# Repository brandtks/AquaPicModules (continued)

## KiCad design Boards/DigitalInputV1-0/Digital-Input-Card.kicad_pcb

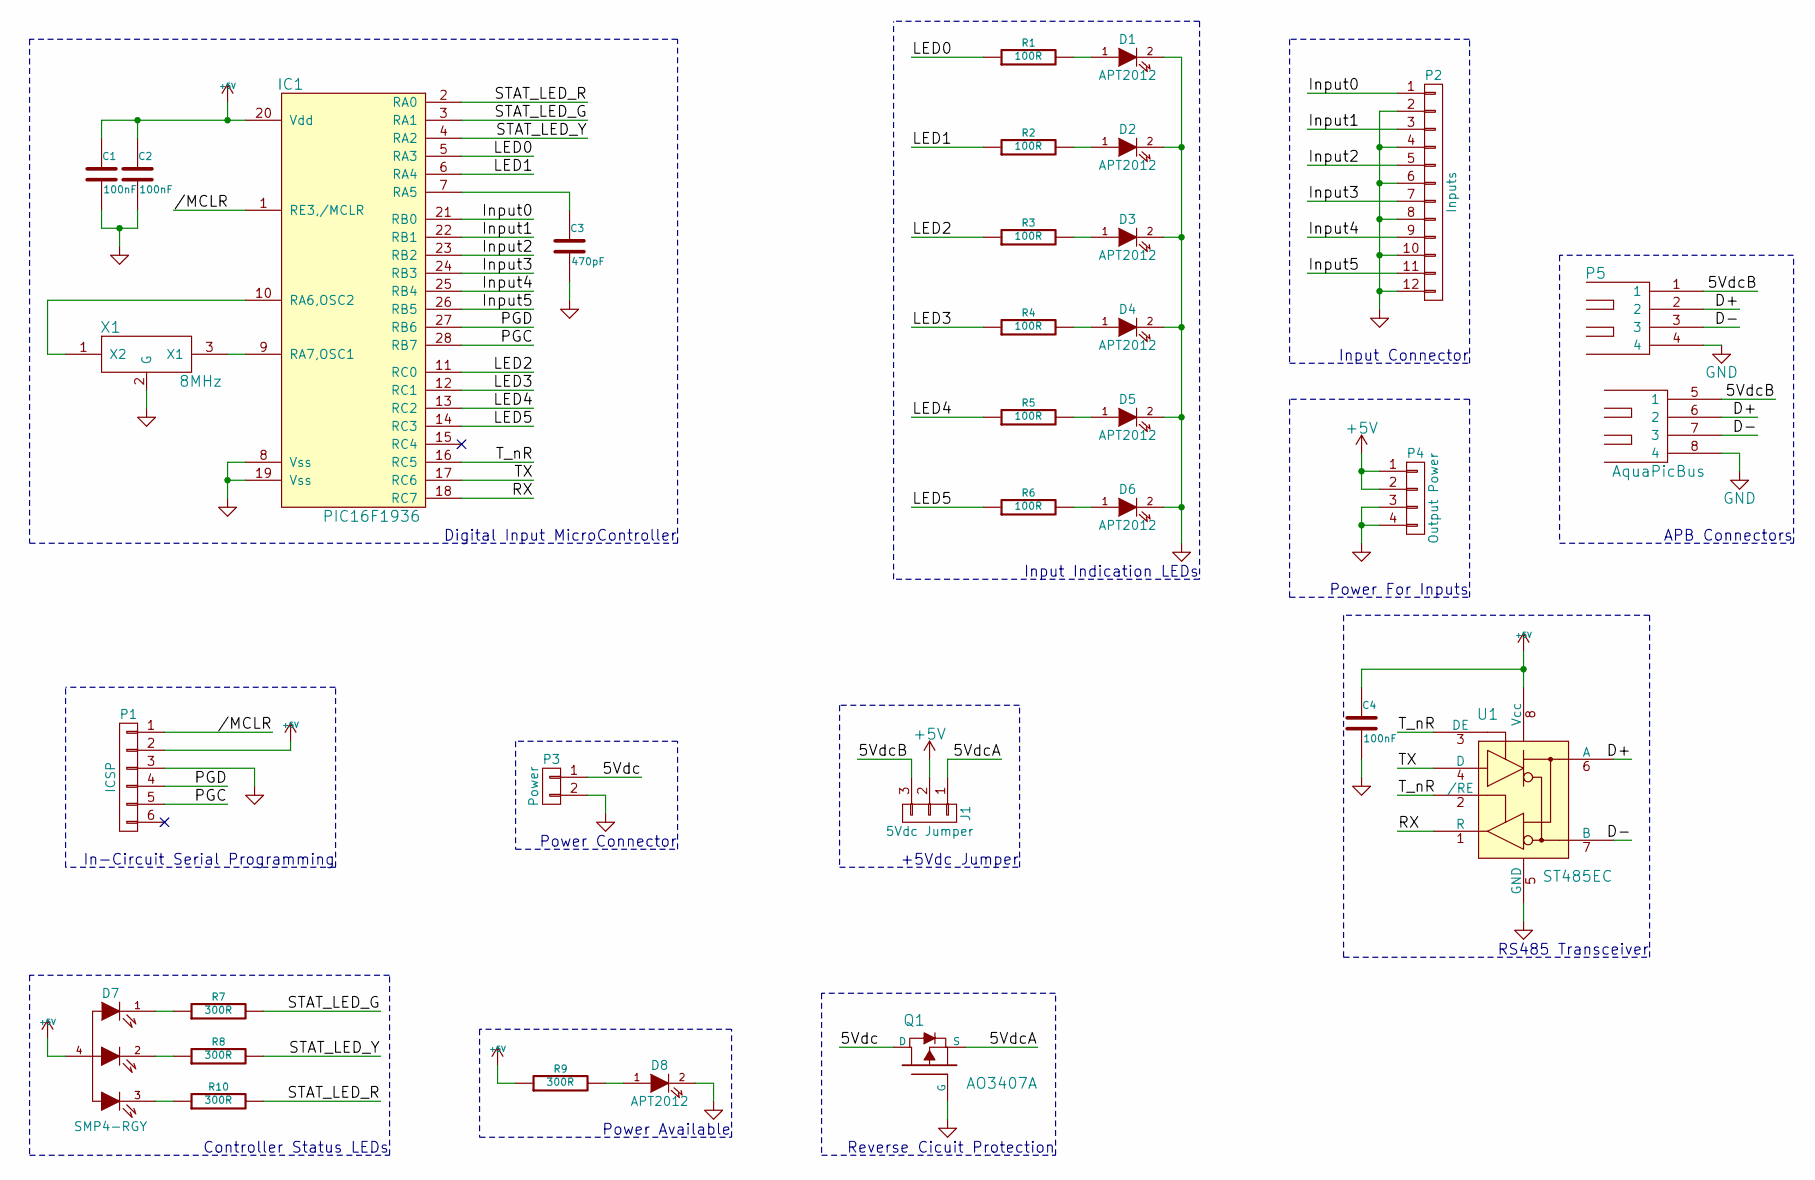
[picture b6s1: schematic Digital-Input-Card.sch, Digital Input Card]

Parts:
C1, C2, C4: 100nF; C_0805
C3: 470pF; C_0805
D1, D2, D3, D4, D5, D6, D8: APT2012; LED-0805
D7: SMP4-RGY; PLCC-4
IC1: PIC16F1936; SOIC-28_7.5x17.9mm_Pitch1.27mm
J1: 5Vdc Jumper; Pin_Header_Straight_1x03
P1: ICSP; Pin_Header_Straight_1x06
P2: Inputs; Screw_Header_1x12
P3: Power; Screw_Header_1x2
P4: Output Power; Screw_Header_1x4
P5: AquaPicBus; USB-1.1_Stacked
Q1: AO3407A; SOT-23
R1, R2, R3, R4, R5, R6: 100R; R_0805
R7, R8, R9, R10: 300R; R_0805
U1: ST485EC; SOIC-8_3.9x4.9mm_Pitch1.27mm
X1: 8MHz; Resonator_3.2x1.3

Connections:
+5V: C1.1, C2.1, C4.1, D7.4, IC1.20 (Vdd), J1.2, P1.2, P4.1, P4.2, R9.1, U1.8 (Vcc)
/5Vdc: P3.1, Q1.3 (D)
/5VdcA: J1.1, Q1.2 (S)
/5VdcB: J1.3, P5.1, P5.5 (1)
//MCLR: IC1.1 (RE3,/MCLR), P1.1
/D+: P5.2, P5.6 (2), U1.6 (A)
/D-: P5.3, P5.7 (3), U1.7 (B)
/Input0: IC1.21 (RB0), P2.1
/Input1: IC1.22 (RB1), P2.3
/Input2: IC1.23 (RB2), P2.5
/Input3: IC1.24 (RB3), P2.7
/Input4: IC1.25 (RB4), P2.9
/Input5: IC1.26 (RB5), P2.11
/LED0: IC1.5 (RA3), R1.1
/LED1: IC1.6 (RA4), R2.1
/LED2: IC1.11 (RC0), R3.1
/LED3: IC1.12 (RC1), R4.1
/LED4: IC1.13 (RC2), R5.1
/LED5: IC1.14 (RC3), R6.1
/PGC: IC1.28 (RB7), P1.5
/PGD: IC1.27 (RB6), P1.4
/RX: IC1.18 (RC7), U1.1 (R)
/STAT_LED_G: IC1.3 (RA1), R7.2
/STAT_LED_R: IC1.2 (RA0), R10.2
/STAT_LED_Y: IC1.4 (RA2), R8.2
/TX: IC1.17 (RC6), U1.4 (D)
/T_nR: IC1.16 (RC5), U1.2 (/RE), U1.3 (DE)
GND: C1.2, C2.2, C3.2, C4.2, D1.2 (K), D2.2 (K), D3.2 (K), D4.2 (K), D5.2 (K), D6.2 (K), D8.2 (K), IC1.8 (Vss), IC1.19 (Vss), P1.3, P2.2, P2.4, P2.6, P2.8, P2.10, P2.12, P3.2, P4.3, P4.4, P5.4, P5.8 (4), Q1.1 (G), U1.5 (GND), X1.2 (G)
unnamed: C3.1, IC1.7 (RA5)
unnamed: D1.1 (A), R1.2
unnamed: D2.1 (A), R2.2
unnamed: D3.1 (A), R3.2
unnamed: D4.1 (A), R4.2
unnamed: D5.1 (A), R5.2
unnamed: D6.1 (A), R6.2
unnamed: D7.1, R7.1
unnamed: D7.2, R8.1
unnamed: D7.3, R10.1
unnamed: D8.1 (A), R9.2
unnamed: IC1.9 (RA7,OSC1), X1.3 (X1)
unnamed: IC1.10 (RA6,OSC2), X1.1 (X2)

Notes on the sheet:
In-Circuit Serial Programming
Input Indication LEDs
Digital Input MicroController
Input Connector
Controller Status LEDs
RS485 Transceiver
Reverse Cicuit Protection
Power Available
+5Vdc Jumper
Power Connector
APB Connectors
Power For Inputs

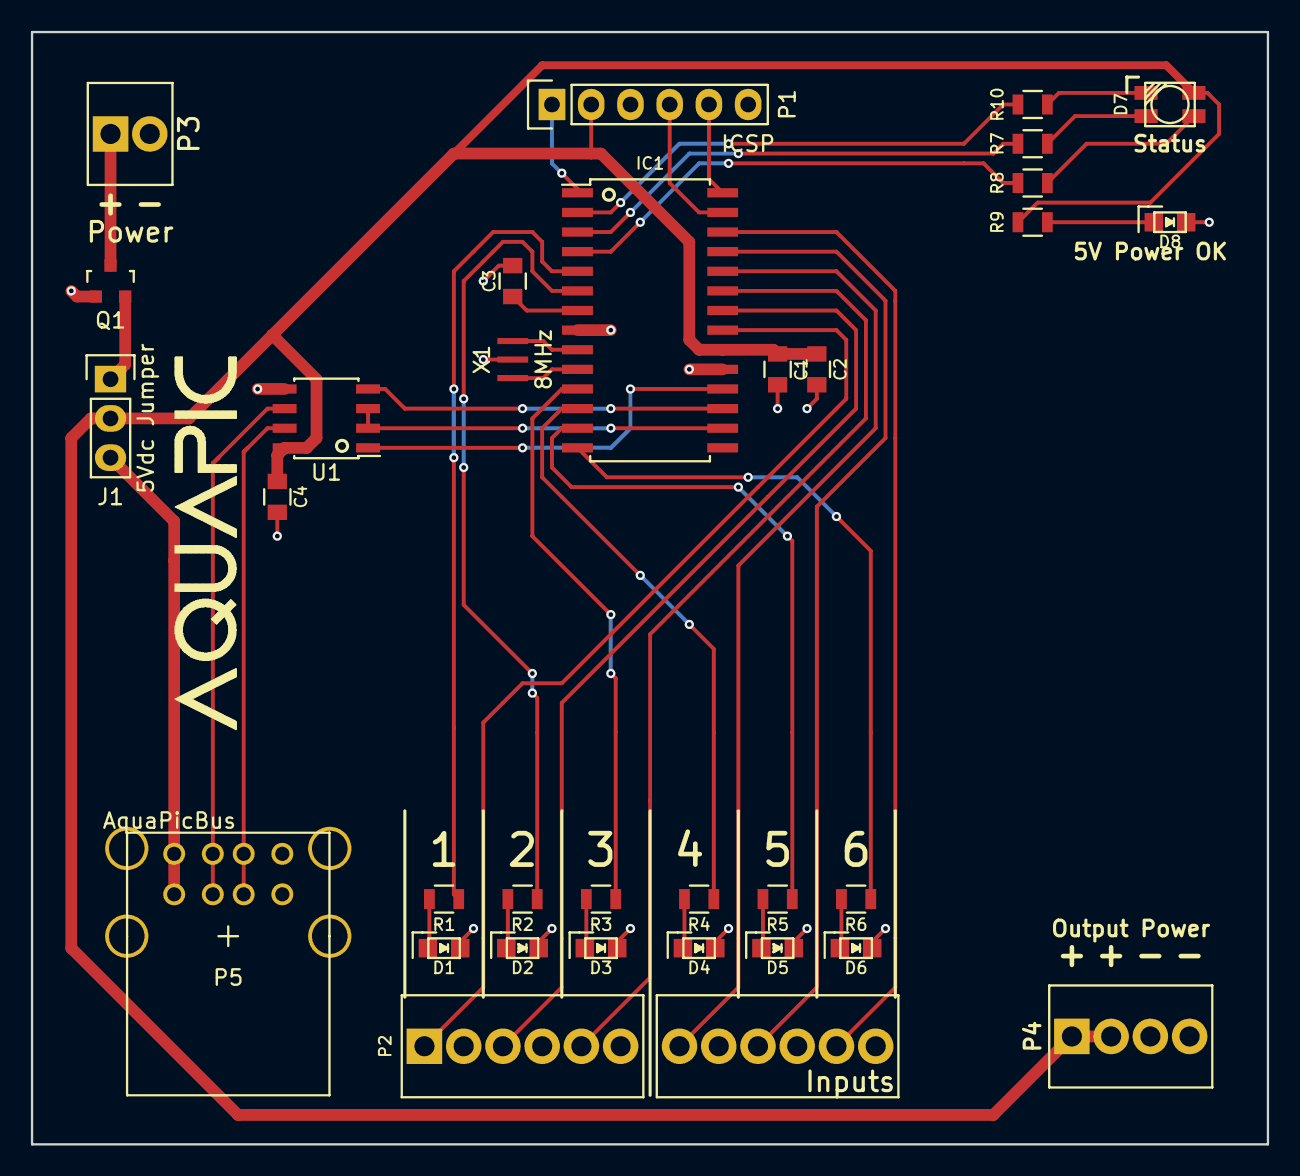
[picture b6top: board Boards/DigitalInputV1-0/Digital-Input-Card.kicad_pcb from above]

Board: 2 copper layers, 80.0 x 72.0 mm, 33 parts (0 on the bottom side), 41 nets.

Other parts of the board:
LOGO: Val**; AquaPic_Logo

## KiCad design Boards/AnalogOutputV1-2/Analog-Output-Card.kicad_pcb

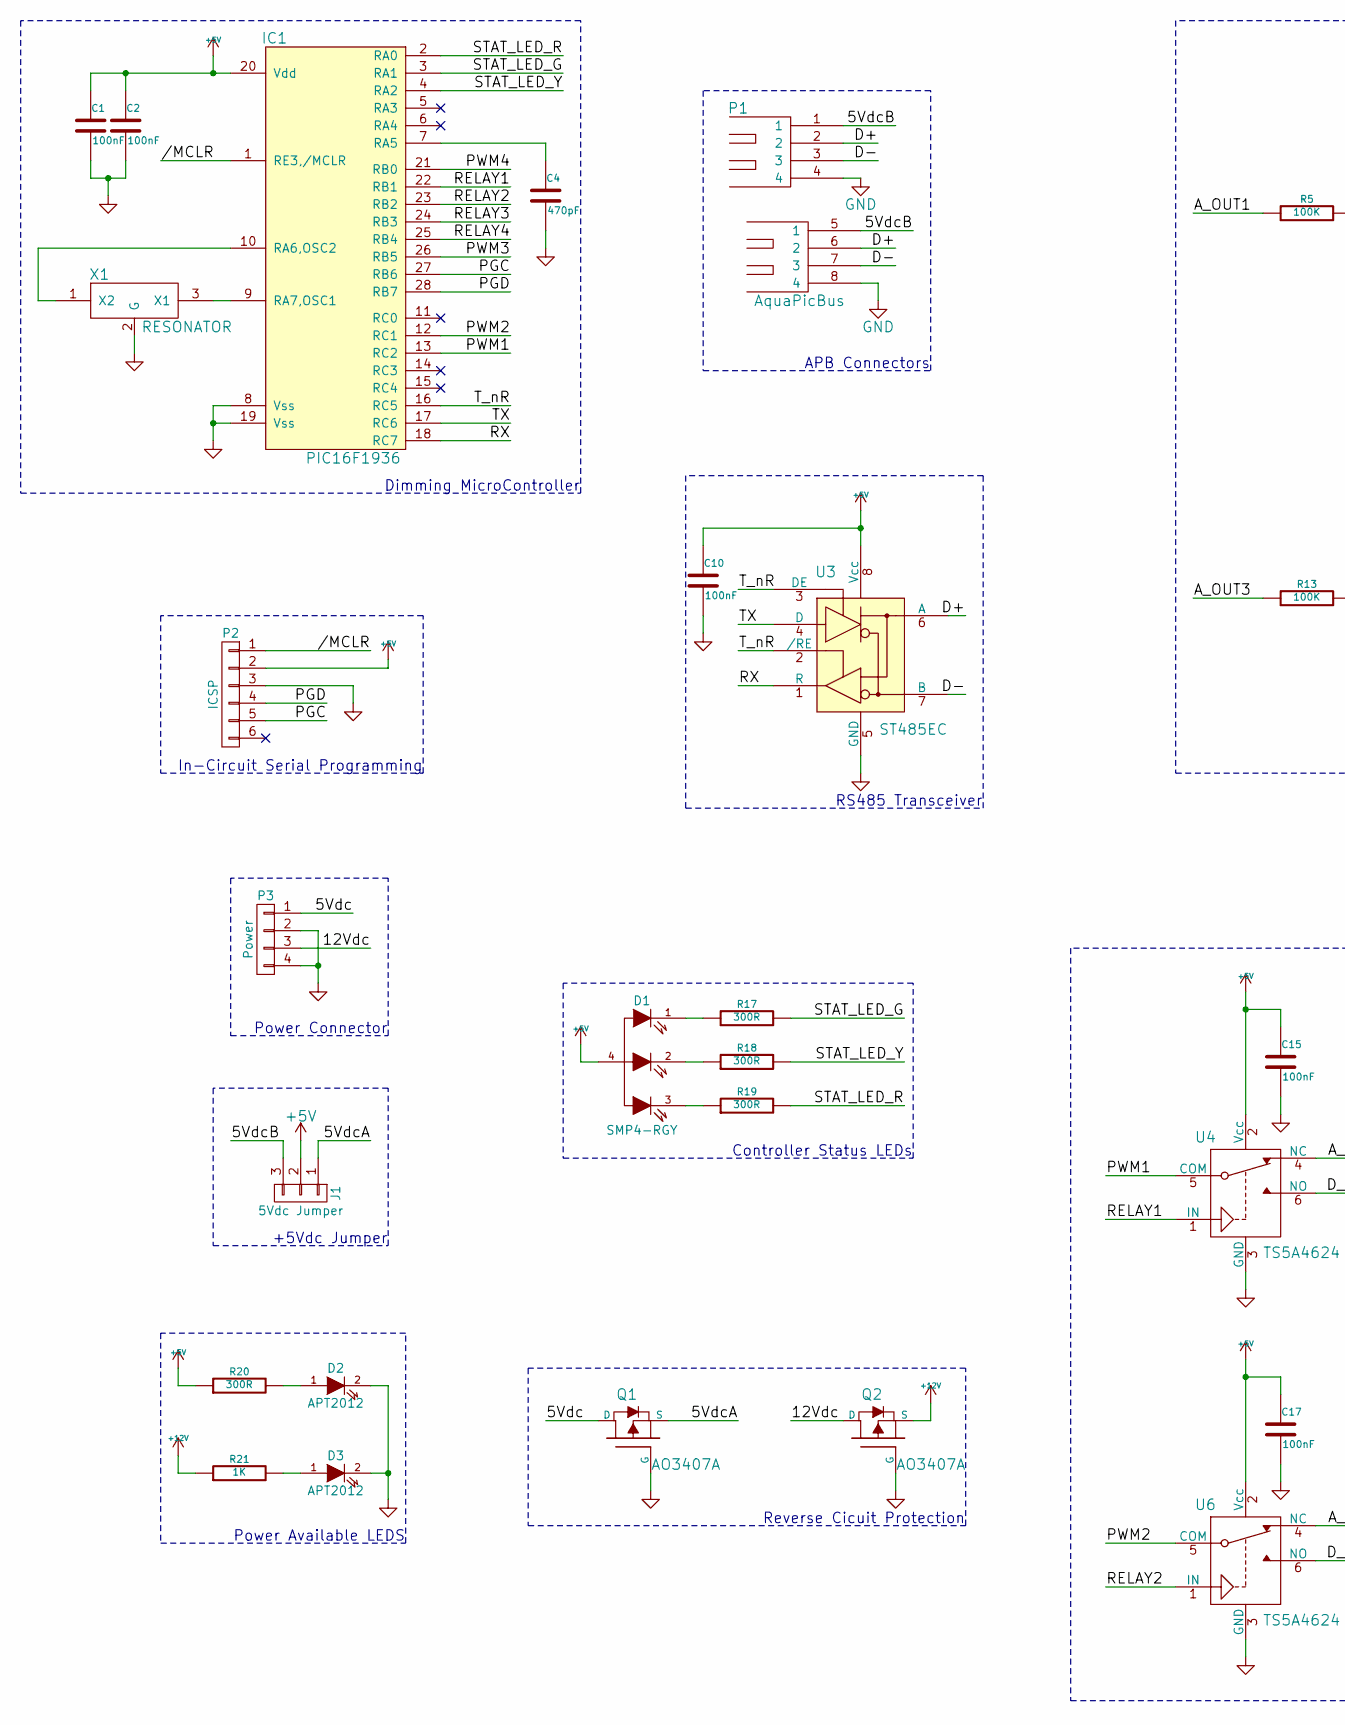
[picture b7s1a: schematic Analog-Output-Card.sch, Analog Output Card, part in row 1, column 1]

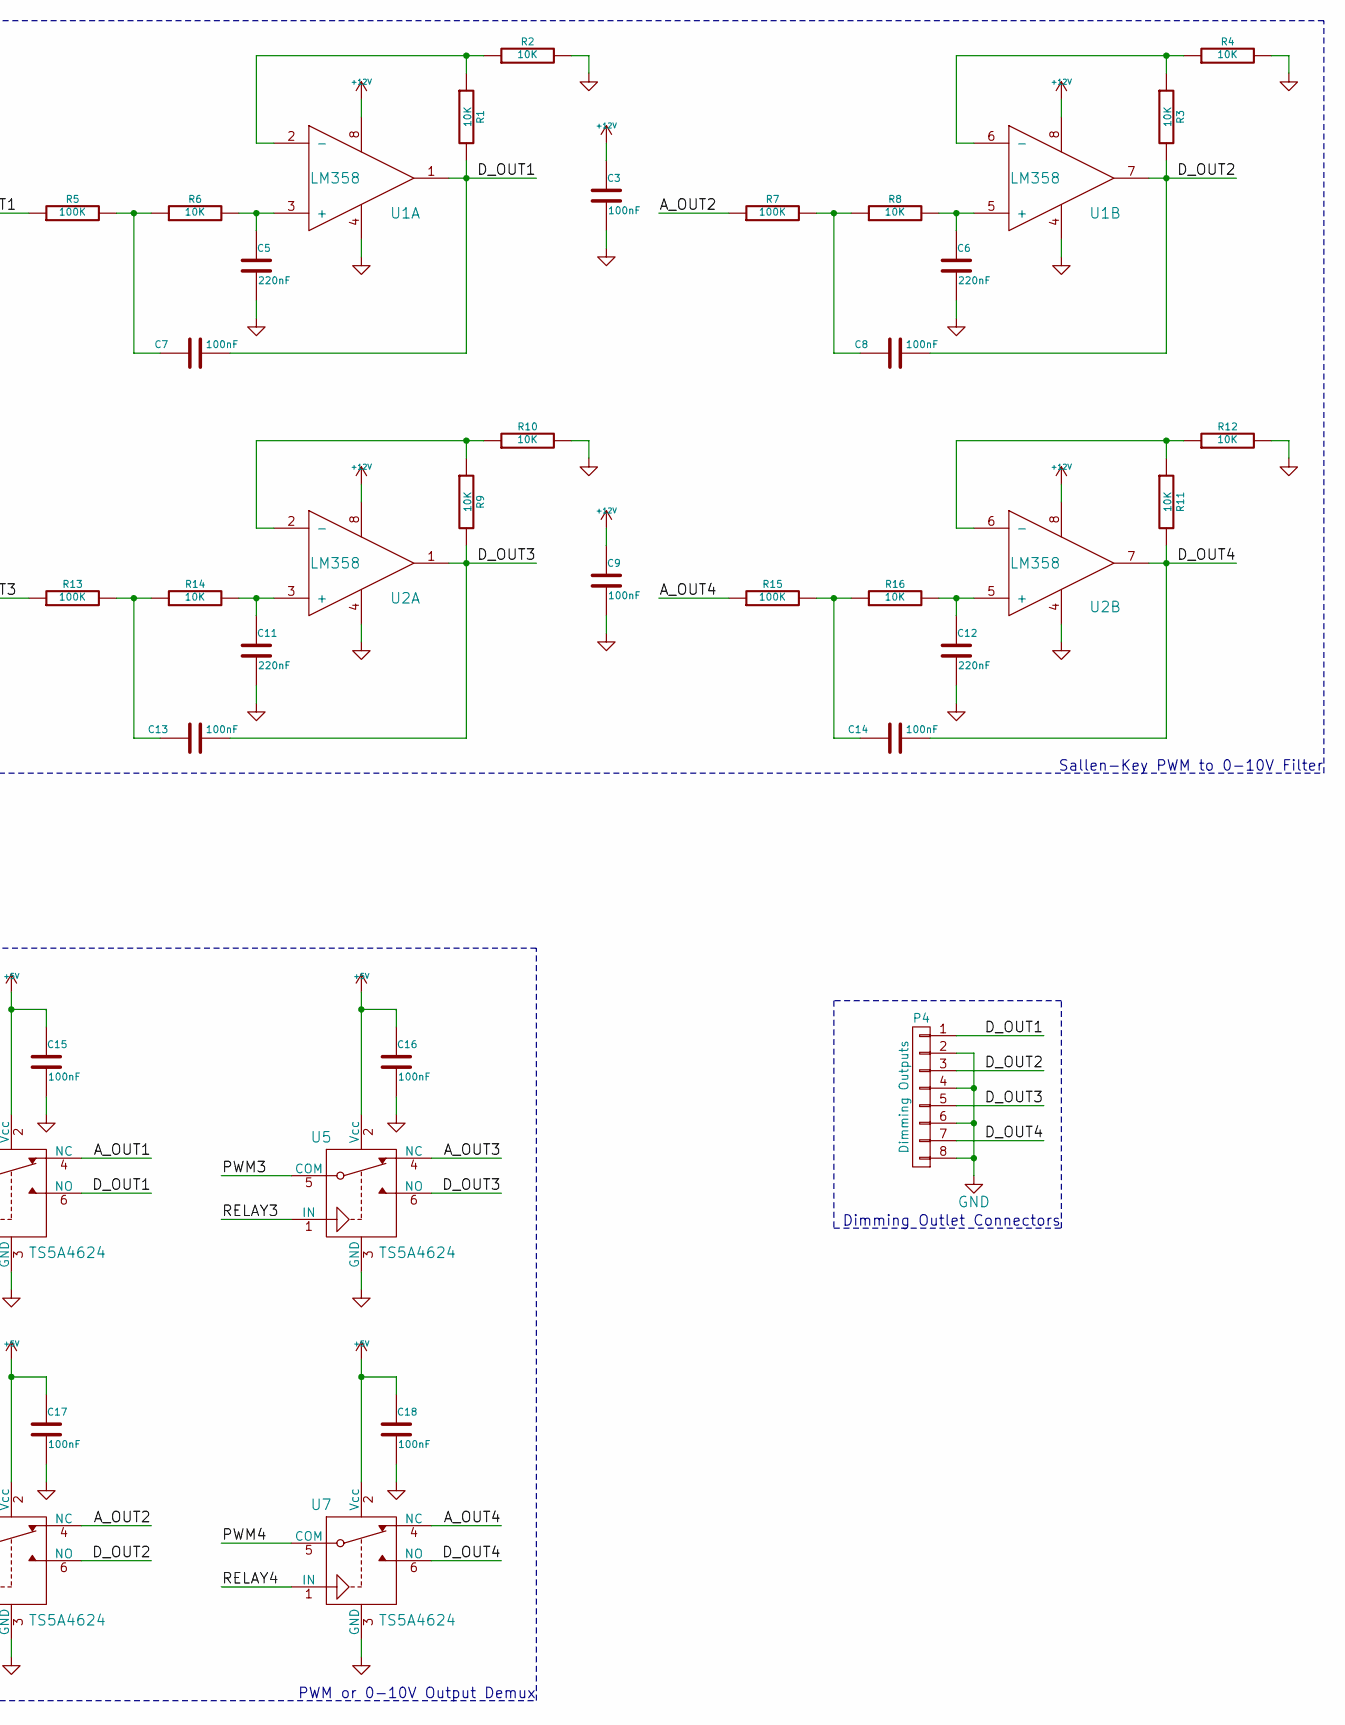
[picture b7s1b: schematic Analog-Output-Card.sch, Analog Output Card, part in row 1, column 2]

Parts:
C1, C2, C3, C7, C8, C9, C10, C13, C14, C15, C16, C17, C18: 100nF; C_0805
C4: 470pF; C_0805
C5, C6, C11, C12: 220nF; C_0805
D1: SMP4-RGY; PLCC-4
D2, D3: APT2012; LED-0805
IC1: PIC16F1936; SOIC-28_7.5x17.9mm_Pitch1.27mm
J1: 5Vdc Jumper; Pin_Header_Straight_1x03
P1: AquaPicBus; USB-1.1_Stacked
P2: ICSP
P3: Power; Screw_Header_1x4
P4: Dimming Outputs; Screw_Header_1x8
Q1, Q2: AO3407A; SOT-23
R1, R2, R3, R4, R6, R8, R9, R10, R11, R12, R14, R16: 10K; R_0805
R5, R7, R13, R15: 100K; R_0805
R17, R18, R19, R20: 300R; R_0805
R21: 1K; R_0805
U1, U2: LM358; TSSOP-8_4.4x3mm_Pitch0.65mm
U3: ST485EC; SOIC-8_3.9x4.9mm_Pitch1.27mm
U4, U5, U6, U7: TS5A4624; TSSOP-6_SC-70-6
X1: RESONATOR

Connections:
+5V: C1.1, C2.1, C10.1, C15.1, C16.1, C17.1, C18.1, D1.4, IC1.20 (Vdd), J1.2, P2.2, R20.1, U3.8 (Vcc), U4.2 (Vcc), U5.2 (Vcc), U6.2 (Vcc), U7.2 (Vcc)
+12V: C3.1, C9.1, Q2.2 (S), R21.1, U1.8, U2.8
/5Vdc: P3.1, Q1.3 (D)
/5VdcA: J1.1, Q1.2 (S)
/5VdcB: J1.3, P1.1, P1.5 (1)
/12Vdc: P3.3, Q2.3 (D)
//MCLR: IC1.1 (RE3,/MCLR), P2.1
/A_OUT1: R5.1, U4.4 (NC)
/A_OUT2: R7.1, U6.4 (NC)
/A_OUT3: R13.1, U5.4 (NC)
/A_OUT4: R15.1, U7.4 (NC)
/D+: P1.2, P1.6 (2), U3.6 (A)
/D-: P1.3, P1.7 (3), U3.7 (B)
/D_OUT1: C7.2, P4.1, R1.2, U1.1, U4.6 (NO)
/D_OUT2: C8.2, P4.3, R3.2, U1.7, U6.6 (NO)
/D_OUT3: C13.2, P4.5, R9.2, U2.1, U5.6 (NO)
/D_OUT4: C14.2, P4.7, R11.2, U2.7, U7.6 (NO)
/PGC: IC1.27 (RB6), P2.5
/PGD: IC1.28 (RB7), P2.4
/PWM1: IC1.13 (RC2), U4.5 (COM)
/PWM2: IC1.12 (RC1), U6.5 (COM)
/PWM3: IC1.26 (RB5), U5.5 (COM)
/PWM4: IC1.21 (RB0), U7.5 (COM)
/RELAY1: IC1.22 (RB1), U4.1 (IN)
/RELAY2: IC1.23 (RB2), U6.1 (IN)
/RELAY3: IC1.24 (RB3), U5.1 (IN)
/RELAY4: IC1.25 (RB4), U7.1 (IN)
/RX: IC1.18 (RC7), U3.1 (R)
/STAT_LED_G: IC1.3 (RA1), R17.2
/STAT_LED_R: IC1.2 (RA0), R19.2
/STAT_LED_Y: IC1.4 (RA2), R18.2
/TX: IC1.17 (RC6), U3.4 (D)
/T_nR: IC1.16 (RC5), U3.2 (/RE), U3.3 (DE)
GND: C1.2, C2.2, C3.2, C4.2, C5.2, C6.2, C9.2, C10.2, C11.2, C12.2, C15.2, C16.2, C17.2, C18.2, D2.2 (K), D3.2 (K), IC1.8 (Vss), IC1.19 (Vss), P1.4, P1.8 (4), P2.3, P3.2, P3.4, P4.2, P4.4, P4.6, P4.8, Q1.1 (G), Q2.1 (G), R2.2, R4.2, R10.2, R12.2, U1.4, U2.4, U3.5 (GND), U4.3 (GND), U5.3 (GND), U6.3 (GND), U7.3 (GND), X1.2 (G)
unnamed: C4.1, IC1.7 (RA5)
unnamed: C5.1, R6.2, U1.3 (+)
unnamed: C6.1, R8.2, U1.5 (+)
unnamed: C7.1, R5.2, R6.1
unnamed: C8.1, R7.2, R8.1
unnamed: C11.1, R14.2, U2.3 (+)
unnamed: C12.1, R16.2, U2.5 (+)
unnamed: C13.1, R13.2, R14.1
unnamed: C14.1, R15.2, R16.1
unnamed: D1.1, R17.1
unnamed: D1.2, R18.1
unnamed: D1.3, R19.1
unnamed: D2.1 (A), R20.2
unnamed: D3.1 (A), R21.2
unnamed: IC1.9 (RA7,OSC1), X1.3 (X1)
unnamed: IC1.10 (RA6,OSC2), X1.1 (X2)
unnamed: R1.1, R2.1, U1.2 (-)
unnamed: R3.1, R4.1, U1.6 (-)
unnamed: R9.1, R10.1, U2.2 (-)
unnamed: R11.1, R12.1, U2.6 (-)

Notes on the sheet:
Sallen-Key PWM to 0-10V Filter
PWM or 0-10V Output Demux
Dimming MicroController
Controller Status LEDs
RS485 Transceiver
In-Circuit Serial Programming
Reverse Cicuit Protection
Power Available LEDS
+5Vdc Jumper
Power Connector
APB Connectors
Dimming Outlet Connectors

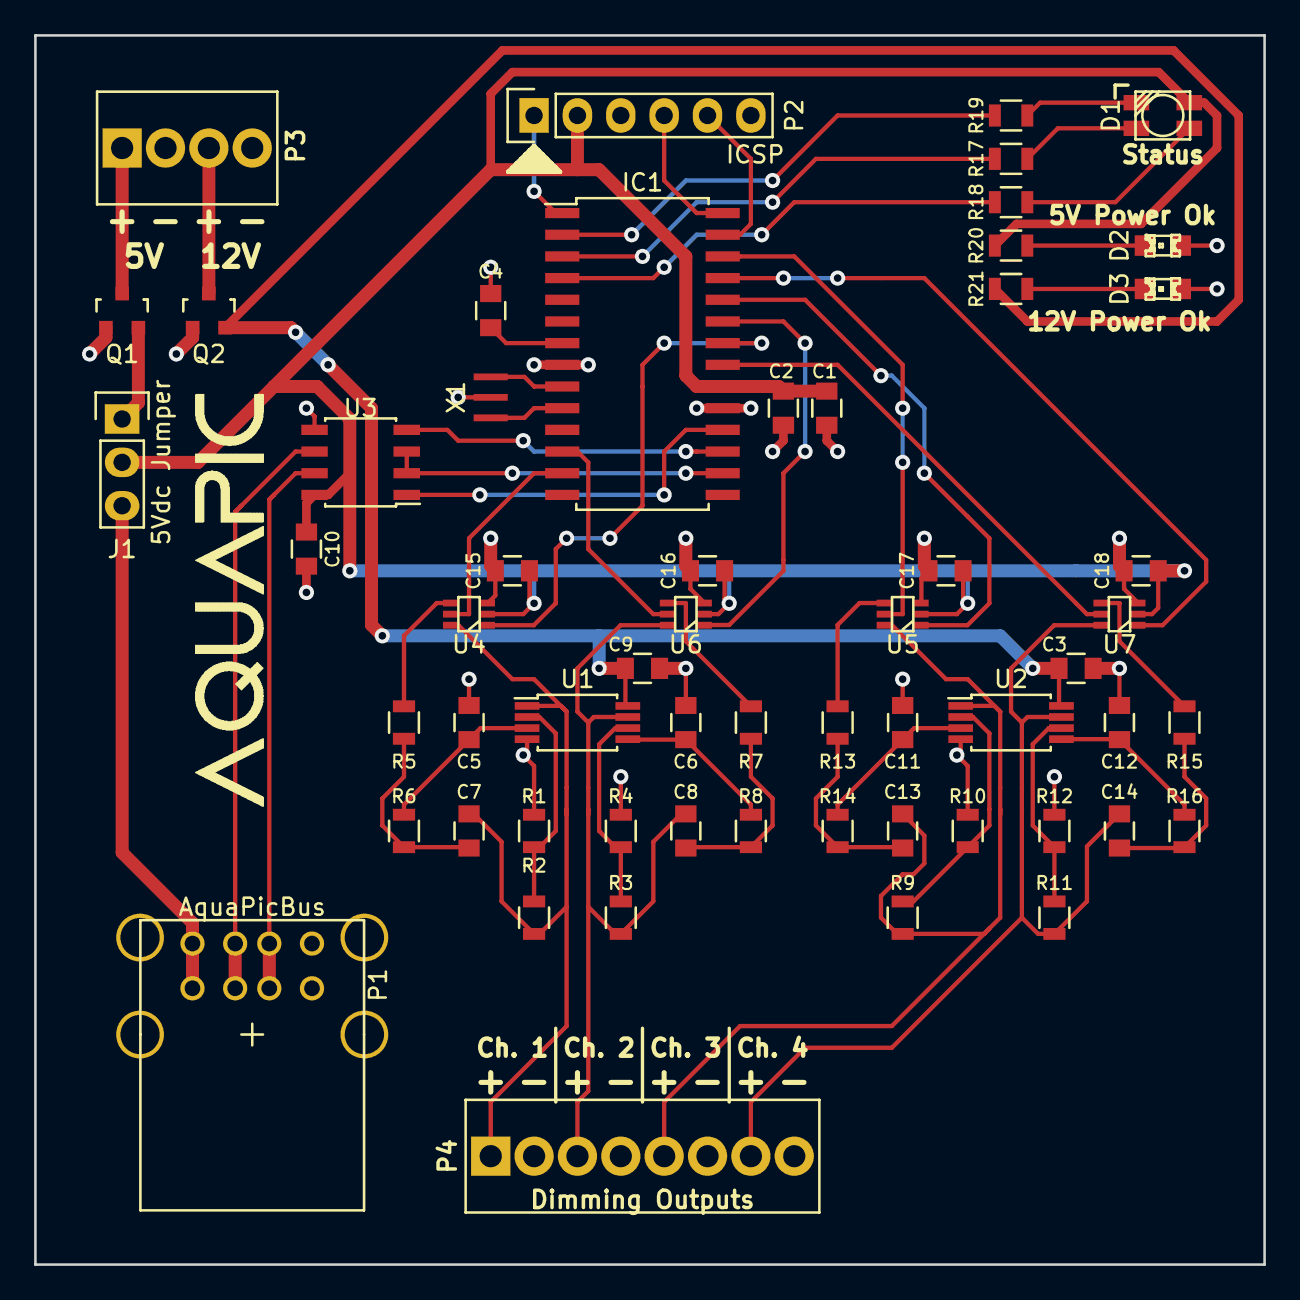
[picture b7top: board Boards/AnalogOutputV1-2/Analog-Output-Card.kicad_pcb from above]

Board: 2 copper layers, 72.0 x 72.0 mm, 59 parts (0 on the bottom side), 54 nets.

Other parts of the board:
LOGO: Val**; AquaPic_Logo

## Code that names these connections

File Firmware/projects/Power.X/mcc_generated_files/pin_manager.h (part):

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*/
/**
  @Summary
    Sets the GPIO pin, RA0, high using LATAbits.LATA0.

  @Description
    Sets the GPIO pin, RA0, high using LATAbits.LATA0.

  @Preconditions
    The RA0 must be set to an output.
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#define CURRENT_5_SetHigh()          ( LATASET = (1 << 0) )
/**
  @Summary
    Sets the GPIO pin, RA0, low using LATAbits.LATA0.

  @Description
    Sets the GPIO pin, RA0, low using LATAbits.LATA0.

  @Preconditions
    The RA0 must be set to an output.
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#define CURRENT_5_SetLow()           ( LATACLR = (1 << 0) )
/**
  @Summary
    Toggles the GPIO pin, RA0, using LATAbits.LATA0.

  @Description
    Toggles the GPIO pin, RA0, using LATAbits.LATA0.

  @Preconditions
    The RA0 must be set to an output.
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#define CURRENT_5_Toggle()           ( LATAINV = (1 << 0) )
/**
  @Summary
    Reads the value of the GPIO pin, RA0.

  @Description
    Reads the value of the GPIO pin, RA0.

  @Preconditions
    None.
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    </code>

*/
#define CURRENT_5_GetValue()         PORTAbits.RA0
/**
  @Summary
    Configures the GPIO pin, RA0, as an input.

  @Description
    Configures the GPIO pin, RA0, as an input.

  @Preconditions
    None.
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#define CURRENT_5_SetDigitalInput()   ( TRISASET = (1 << 0) )
/**
  @Summary
    Configures the GPIO pin, RA0, as an output.

  @Description
    Configures the GPIO pin, RA0, as an output.

  @Preconditions
    None.
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#define CURRENT_5_SetDigitalOutput()   ( TRISACLR = (1 << 0) )
/**
  @Summary
    Sets the GPIO pin, RA1, high using LATAbits.LATA1.

  @Description
    Sets the GPIO pin, RA1, high using LATAbits.LATA1.

  @Preconditions
    The RA1 must be set to an output.
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#define CURRENT_4_SetHigh()          ( LATASET = (1 << 1) )
/**
  @Summary
    Sets the GPIO pin, RA1, low using LATAbits.LATA1.

  @Description
    Sets the GPIO pin, RA1, low using LATAbits.LATA1.

  @Preconditions
    The RA1 must be set to an output.
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#define CURRENT_4_SetLow()           ( LATACLR = (1 << 1) )
/**
  @Summary
    Toggles the GPIO pin, RA1, using LATAbits.LATA1.

  @Description
    Toggles the GPIO pin, RA1, using LATAbits.LATA1.

  @Preconditions
    The RA1 must be set to an output.
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#define CURRENT_4_Toggle()           ( LATAINV = (1 << 1) )
/**
  @Summary
    Reads the value of the GPIO pin, RA1.

  @Description
    Reads the value of the GPIO pin, RA1.

  @Preconditions
    None.
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    </code>

*/
#define CURRENT_4_GetValue()         PORTAbits.RA1
/**
  @Summary
    Configures the GPIO pin, RA1, as an input.

  @Description
    Configures the GPIO pin, RA1, as an input.

  @Preconditions
    None.
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#define CURRENT_4_SetDigitalInput()   ( TRISASET = (1 << 1) )
/**
  @Summary
    Configures the GPIO pin, RA1, as an output.

  @Description
    Configures the GPIO pin, RA1, as an output.

  @Preconditions
    None.
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#define RELAY_3_SetDigitalOutput()   ( TRISACLR = (1 << 10) )
/**
  @Summary
    Sets the GPIO pin, RA4, high using LATAbits.LATA4.

  @Description
    Sets the GPIO pin, RA4, high using LATAbits.LATA4.

  @Preconditions
    The RA4 must be set to an output.
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#define RELAY_8_SetHigh()          ( LATASET = (1 << 4) )
/**
  @Summary
    Sets the GPIO pin, RA4, low using LATAbits.LATA4.

  @Description
    Sets the GPIO pin, RA4, low using LATAbits.LATA4.

  @Preconditions
    The RA4 must be set to an output.
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#define RELAY_8_SetLow()           ( LATACLR = (1 << 4) )
/**
  @Summary
    Toggles the GPIO pin, RA4, using LATAbits.LATA4.

  @Description
    Toggles the GPIO pin, RA4, using LATAbits.LATA4.

  @Preconditions
    The RA4 must be set to an output.
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#define RELAY_8_Toggle()           ( LATAINV = (1 << 4) )
/**
  @Summary
    Reads the value of the GPIO pin, RA4.

  @Description
    Reads the value of the GPIO pin, RA4.

  @Preconditions
    None.
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    </code>

*/
#define RELAY_8_GetValue()         PORTAbits.RA4
/**
  @Summary
    Configures the GPIO pin, RA4, as an input.

  @Description
    Configures the GPIO pin, RA4, as an input.

  @Preconditions
    None.
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#define RELAY_8_SetDigitalInput()   ( TRISASET = (1 << 4) )
/**
  @Summary
    Configures the GPIO pin, RA4, as an output.

  @Description
    Configures the GPIO pin, RA4, as an output.

  @Preconditions
    None.
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#define RELAY_8_SetDigitalOutput()   ( TRISACLR = (1 << 4) )
/**
  @Summary
    Sets the GPIO pin, RA7, high using LATAbits.LATA7.

  @Description
    Sets the GPIO pin, RA7, high using LATAbits.LATA7.

  @Preconditions
    The RA7 must be set to an output.
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#define RELAY_2_SetHigh()          ( LATASET = (1 << 7) )
/**
  @Summary
    Sets the GPIO pin, RA7, low using LATAbits.LATA7.

  @Description
    Sets the GPIO pin, RA7, low using LATAbits.LATA7.

  @Preconditions
    The RA7 must be set to an output.
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#define RELAY_2_SetLow()           ( LATACLR = (1 << 7) )
/**
  @Summary
    Toggles the GPIO pin, RA7, using LATAbits.LATA7.

  @Description
    Toggles the GPIO pin, RA7, using LATAbits.LATA7.

  @Preconditions
    The RA7 must be set to an output.
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#define RELAY_2_Toggle()           ( LATAINV = (1 << 7) )
/**
  @Summary
    Reads the value of the GPIO pin, RA7.

  @Description
    Reads the value of the GPIO pin, RA7.

  @Preconditions
    None.
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    </code>

*/
#define RELAY_2_GetValue()         PORTAbits.RA7
/**
  @Summary
    Configures the GPIO pin, RA7, as an input.

  @Description
    Configures the GPIO pin, RA7, as an input.

  @Preconditions
    None.
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#define RELAY_2_SetDigitalInput()   ( TRISASET = (1 << 7) )
/**
  @Summary
    Configures the GPIO pin, RA7, as an output.

  @Description
    Configures the GPIO pin, RA7, as an output.

  @Preconditions
    None.
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#define RELAY_2_SetDigitalOutput()   ( TRISACLR = (1 << 7) )
/**
  @Summary
    Sets the GPIO pin, RB0, high using LATBbits.LATB0.

  @Description
    Sets the GPIO pin, RB0, high using LATBbits.LATB0.

  @Preconditions
    The RB0 must be set to an output.
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#define CURRENT_3_SetHigh()          ( LATBSET = (1 << 0) )
/**
  @Summary
    Sets the GPIO pin, RB0, low using LATBbits.LATB0.

  @Description
    Sets the GPIO pin, RB0, low using LATBbits.LATB0.

  @Preconditions
    The RB0 must be set to an output.
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#define CURRENT_3_SetLow()           ( LATBCLR = (1 << 0) )
/**
  @Summary
    Toggles the GPIO pin, RB0, using LATBbits.LATB0.

  @Description
    Toggles the GPIO pin, RB0, using LATBbits.LATB0.

  @Preconditions
    The RB0 must be set to an output.
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#define CURRENT_3_Toggle()           ( LATBINV = (1 << 0) )
/**
  @Summary
    Reads the value of the GPIO pin, RB0.

  @Description
    Reads the value of the GPIO pin, RB0.

  @Preconditions
    None.
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    </code>

*/
#define CURRENT_3_GetValue()         PORTBbits.RB0
/**
  @Summary
    Configures the GPIO pin, RB0, as an input.

  @Description
    Configures the GPIO pin, RB0, as an input.

  @Preconditions
    None.
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#define CURRENT_3_SetDigitalInput()   ( TRISBSET = (1 << 0) )
/**
  @Summary
    Configures the GPIO pin, RB0, as an output.

  @Description
    Configures the GPIO pin, RB0, as an output.

  @Preconditions
    None.
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#define CURRENT_3_SetDigitalOutput()   ( TRISBCLR = (1 << 0) )
/**
  @Summary
    Sets the GPIO pin, RB1, high using LATBbits.LATB1.

  @Description
    Sets the GPIO pin, RB1, high using LATBbits.LATB1.

  @Preconditions
    The RB1 must be set to an output.
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#define CURRENT_2_SetHigh()          ( LATBSET = (1 << 1) )
/**
  @Summary
    Sets the GPIO pin, RB1, low using LATBbits.LATB1.

  @Description
    Sets the GPIO pin, RB1, low using LATBbits.LATB1.

  @Preconditions
    The RB1 must be set to an output.
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#define CURRENT_2_SetLow()           ( LATBCLR = (1 << 1) )
/**
  @Summary
    Toggles the GPIO pin, RB1, using LATBbits.LATB1.

  @Description
    Toggles the GPIO pin, RB1, using LATBbits.LATB1.

  @Preconditions
    The RB1 must be set to an output.
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#define CURRENT_2_Toggle()           ( LATBINV = (1 << 1) )
/**
  @Summary
    Reads the value of the GPIO pin, RB1.

  @Description
    Reads the value of the GPIO pin, RB1.

  @Preconditions
    None.
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    </code>

*/
#define CURRENT_2_GetValue()         PORTBbits.RB1
/**
  @Summary
    Configures the GPIO pin, RB1, as an input.

  @Description
    Configures the GPIO pin, RB1, as an input.

  @Preconditions
    None.
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#define CURRENT_2_SetDigitalInput()   ( TRISBSET = (1 << 1) )
/**
  @Summary
    Configures the GPIO pin, RB1, as an output.

  @Description
    Configures the GPIO pin, RB1, as an output.

  @Preconditions
    None.
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#define CURRENT_2_SetDigitalOutput()   ( TRISBCLR = (1 << 1) )
/**
  @Summary
    Sets the GPIO pin, RB2, high using LATBbits.LATB2.

  @Description
    Sets the GPIO pin, RB2, high using LATBbits.LATB2.

  @Preconditions
    The RB2 must be set to an output.
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#define CURRENT_1_SetHigh()          ( LATBSET = (1 << 2) )
/**
  @Summary
    Sets the GPIO pin, RB2, low using LATBbits.LATB2.

  @Description
    Sets the GPIO pin, RB2, low using LATBbits.LATB2.

  @Preconditions
    The RB2 must be set to an output.
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#define CURRENT_1_SetLow()           ( LATBCLR = (1 << 2) )
/**
  @Summary
    Toggles the GPIO pin, RB2, using LATBbits.LATB2.
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
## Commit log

2015-09-16 fixed A/D clock in powerControl.c
2015-11-19 added micros for LEDs added support to disable to current sensing
2015-12-22 change message structure sent by master rename Power directory
2015-12-29 Added source for analog and digital input cards Renamed Analog output card Various cleanup
2015-12-29 cleanup
2015-12-29 updated README.txt
2016-01-13 fixed preprocessor directives
2016-02-09 added outlet states to status message
2016-02-14 working on AquaPic Bus errors
2016-02-23 updated cards with new aquapic bus slave code
2016-02-24 attempted bug fixes with AquaPic Bus slave
2016-07-22 replace address detection from 9th bit to time based
2016-07-24 comment clean up
2016-08-17 moved analog input from PIC16F1827 to PIC16F1783
2016-08-17 committed before saving
2017-03-10 updating
2017-04-05 refactoring analog-input
2017-04-05 refactoring
2017-04-06 untest refactor
2017-04-07 added crude testing
2017-04-07 cleaned up after erronous adds from testing AquaPicBus
2017-04-07 updated .gitignore
2017-04-07 more removing oddball files
2017-04-23 continued work on abstraction, focus on led and adc
2017-04-23 refactored analog output card
2017-05-06 finished refactoring analog output
2017-05-06 refactored digital input
2017-05-06 refactored power
2017-05-06 added project files and update readme
2017-05-06 fixed readme
2017-05-06 fixed website list in readme
2017-05-18 fixed aquapic test make and updated readme
2017-06-26 work on generalized makefile
2017-06-28 work on makefiles
2017-06-28 added makefiles
2017-06-28 added makefile
2017-10-29 small makefile change
2017-10-30 moved files around
2017-10-30 included board design
2017-10-30 removed unneeded boards
2017-10-30 added readmes
2017-10-30 removed unnecessary files
2017-10-30 removed more unnecessary files
2017-10-30 removed modules without firmware
2017-10-31 started ananlog input revision 2
2017-11-01 finished rev 2 for analog input
2017-11-01 documentation for rev 2 analog input
2017-11-10 work on ai v2
2017-11-10 cleanup symbolic links
2017-11-11 work on ai v2 firmware
2017-11-11 started i2c driver
2017-11-12 worked on i2c driver and board design
2017-11-13 started development with PIC32MM
2017-11-14 work on AnalogInputCard
2017-11-14 organized libraries by arch
2017-11-14 started work on 32bit ai firmware
2017-11-16 Added some documentation
2017-11-16 finished board layout for ai
2017-11-17 work on firmware for ai
2017-11-19 finished rough alpha firmware for analog input
2017-11-23 started working on compiling
2017-11-23 working on building
2017-11-24 finished command line building and fixing other cards
2017-11-24 fixed extension for notes
2017-11-24 fixed extention for notes:
2017-11-24 added missing readme
2017-11-24 fixed silkscreen on analog input
2017-11-24 regenerated gerbers
2017-11-24 added ai schematic image
2017-11-24 cleaning up a few things
2017-11-24 started work on pH/ORP card redesign
2017-11-24 worked on pH ORP board layout
2017-11-24 added ph orp notes
2017-11-25 added firmware for the pH ORP Card
2017-11-25 finished pH ORP BOM
2017-11-25 something changed in schematic
2017-11-25 fixed led pin startup state
2017-11-25 fixed readmes
2017-11-25 added some notes
2017-11-25 Added WorkList.md
2017-11-26 added enable disable for ph isolation
2017-11-26 kicad updating something
2017-11-26 starting refactoring analog output
2017-12-01 fixed pinout on analog input card
2017-12-02 working on Analog Output card
2017-12-02 updated gitignore for csv files
2017-12-03 worked on Analog Output Cardboard layout finished
2017-12-03 finished firmware for ananlog output card
2017-12-03 added header files to source control
2017-12-03 removed source files
2017-12-03 added readme to analog output
2017-12-03 fixed setting pwm value
2017-12-03 removed Analog-Output-Card.csv
2017-12-03 adding nvm
2017-12-03 added EEPROM simulation
2017-12-03 fixed uninitialized nvm reading
2017-12-05 fixed license issue
2017-12-05 Dropbox isn't the most reliable
2017-12-10 refactored Digital Input to PIC32
2017-12-10 added renamed file
2017-12-10 updated digital input bom
2017-12-10 worked on charlieplexed led circuit design
2017-12-12 working on refactoring power to PIC32
2017-12-13 working on power refactor
2017-12-17 finished alpha power firmware
2017-12-17 fixed apb addressing
2017-12-18 working on power pcb
2018-03-08 must have made changes to some schematics
2018-06-05 finished power board layout and fixed pin mappings
2018-06-06 added power bom
2018-07-31 fixed placement on boards so everything is mostly in the same spot
2018-08-14 more work on uniformity between boards
2018-08-24 Cleanup on Power PCB
2018-09-30 working on analog input bom
2018-09-30 upgrade pH ORP to KiCAD 5
2018-09-30 changed power supply isolation to n channel mosfet, schematic is now bom
2018-09-30 removed tracking bom and schematics
2018-09-30 changed power supply switch from p channel to n channel
2018-09-30 migrated digital input to KiCAD 5
2018-09-30 fixed icsp footprint
2018-10-18 updated analog input to kicad 5
2018-10-18 renamed analog input and output directories
2018-10-18 analog output bom is not controlled by schematic
2018-10-18 analog input bom is now controlled by schematic
2018-10-18 renamed Power directory
2018-10-18 Power bom is now controlled by schematic
2018-10-18 generated BOMs
